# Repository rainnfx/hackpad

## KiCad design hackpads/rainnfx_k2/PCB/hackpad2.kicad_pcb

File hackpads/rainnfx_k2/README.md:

# rainnfx_k2

This is my second attempt at making a solid macropad, this time I'm going with a much more simple, yet effective approach.

## Features:
- EC11 Rotary encoder
- 6 Keys

## CAD Model:
Everything fits together using 4 M3 Bolts and heatset inserts.

It has 3 separate printed pieces. The base where the PCB will sit, the top cover, and a custom knob for the encoder.

[ img will go here ]

Made in Shapr3d.

## PCB
Here's my PCB! It was made in KiCad.

Schematic
[ img ]

PCB
[ img ]

## Firmware Overview
This hackpad uses [QMK](https://qmk.fm/) firmware for everything. 

- the rotary encoder changes volume. press to mute
- The 6 keys currently are sort of placeholders, since I have no clue what I'll assign them to yet (probably to open some apps or smth)!

## BOM:
Here should be everything you need to make this hackpad

- 6x Cherry MX Switches
- 6x DSA Keycaps
- 4x M3x5x4 Heatset inserts
- 4x M3x16mm SHCS Bolts
- 6x [MMSD4148T1G](https://www.digikey.ca/en/products/detail/onsemi/mmsd4148t1g/919705) Diodes.
- 1x [EC11E15204A3](https://www.digikey.ca/en/products/detail/alps-alpine/ec11e15204a3/21721644)
- 1x XIAO RP2040
- 1x Case (3 printed parts)

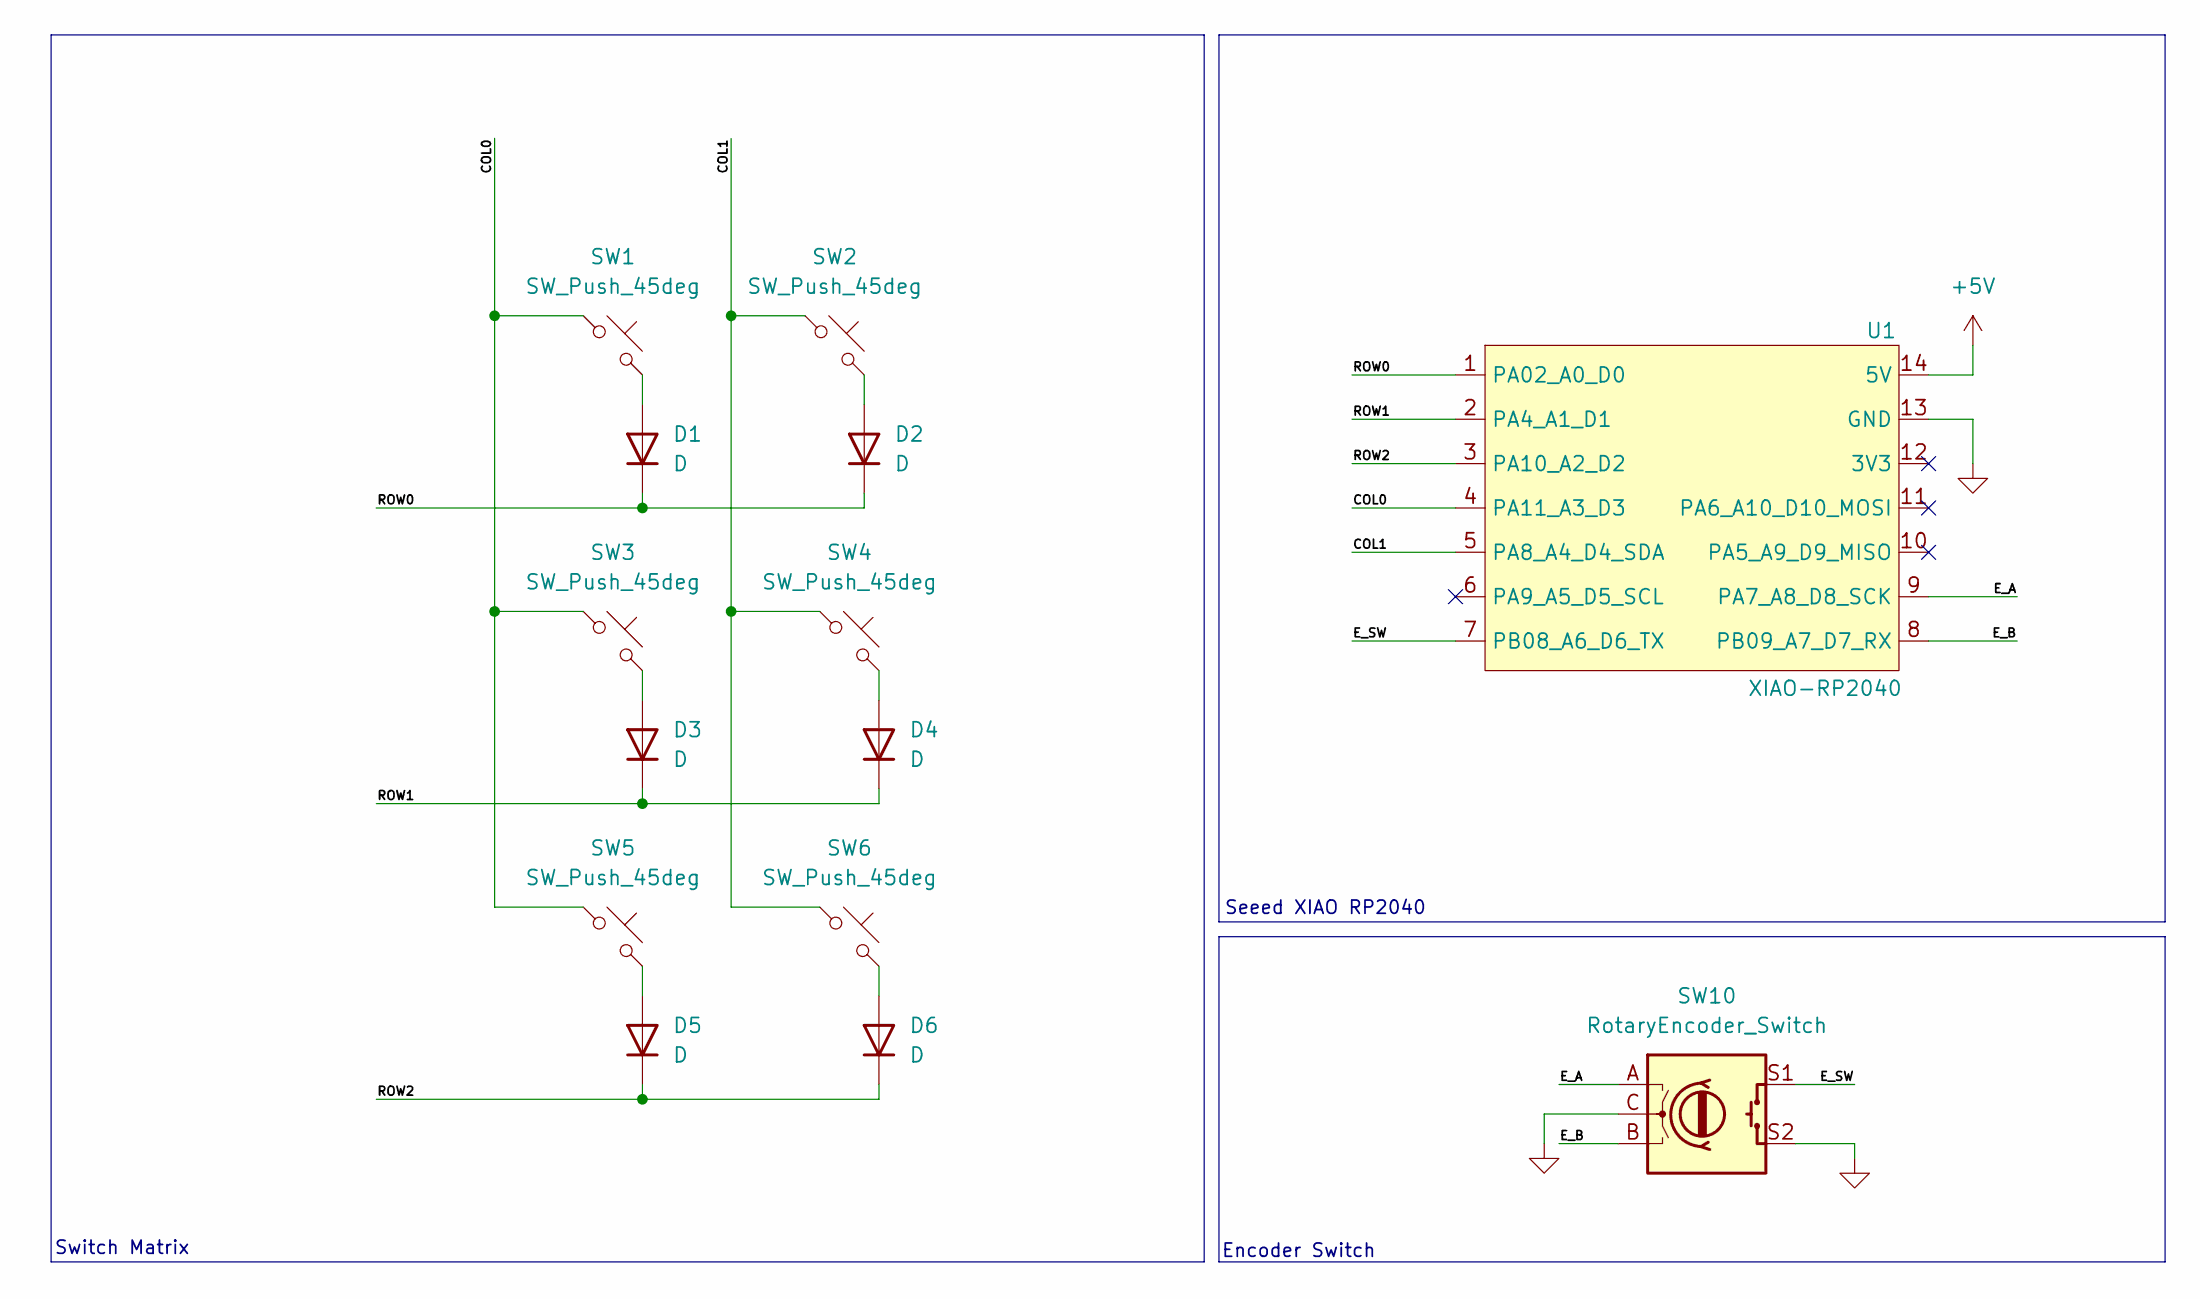
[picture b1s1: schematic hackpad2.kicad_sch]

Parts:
D1, D2, D3, D4, D5, D6: D; SOD3716X135N
SW1, SW2, SW3, SW4, SW5, SW6: SW_Push_45deg; SW_Cherry_MX_1.00u_PCB
SW10: RotaryEncoder_Switch; RotaryEncoder_Alps_EC11E-Switch_Vertical_H20mm
U1: XIAO-RP2040; MOUDLE14P-SMD-2.54-21X17.8MM

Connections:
+5V: U1.14 (5V)
/COL0: SW1.1, SW3.1, SW5.1, U1.4 (PA11_A3_D3)
/COL1: SW2.1, SW4.1, SW6.1, U1.5 (PA8_A4_D4_SDA)
/COL2: U1.6 (PA9_A5_D5_SCL)
/E_A: SW10.A, U1.9 (PA7_A8_D8_SCK)
/E_B: SW10.B, U1.8 (PB09_A7_D7_RX)
/E_SW: SW10.S1, U1.7 (PB08_A6_D6_TX)
/ROW0: D1.1 (K), D2.1 (K), U1.1 (PA02_A0_D0)
/ROW1: D3.1 (K), D4.1 (K), U1.2 (PA4_A1_D1)
/ROW2: D5.1 (K), D6.1 (K), U1.3 (PA10_A2_D2)
GND: SW10.C, SW10.S2, U1.13 (GND)
unnamed: D1.2 (A), SW1.2
unnamed: D2.2 (A), SW2.2
unnamed: D3.2 (A), SW3.2
unnamed: D4.2 (A), SW4.2
unnamed: D5.2 (A), SW5.2
unnamed: D6.2 (A), SW6.2

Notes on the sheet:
Seeed XIAO RP2040
Encoder Switch
Switch Matrix

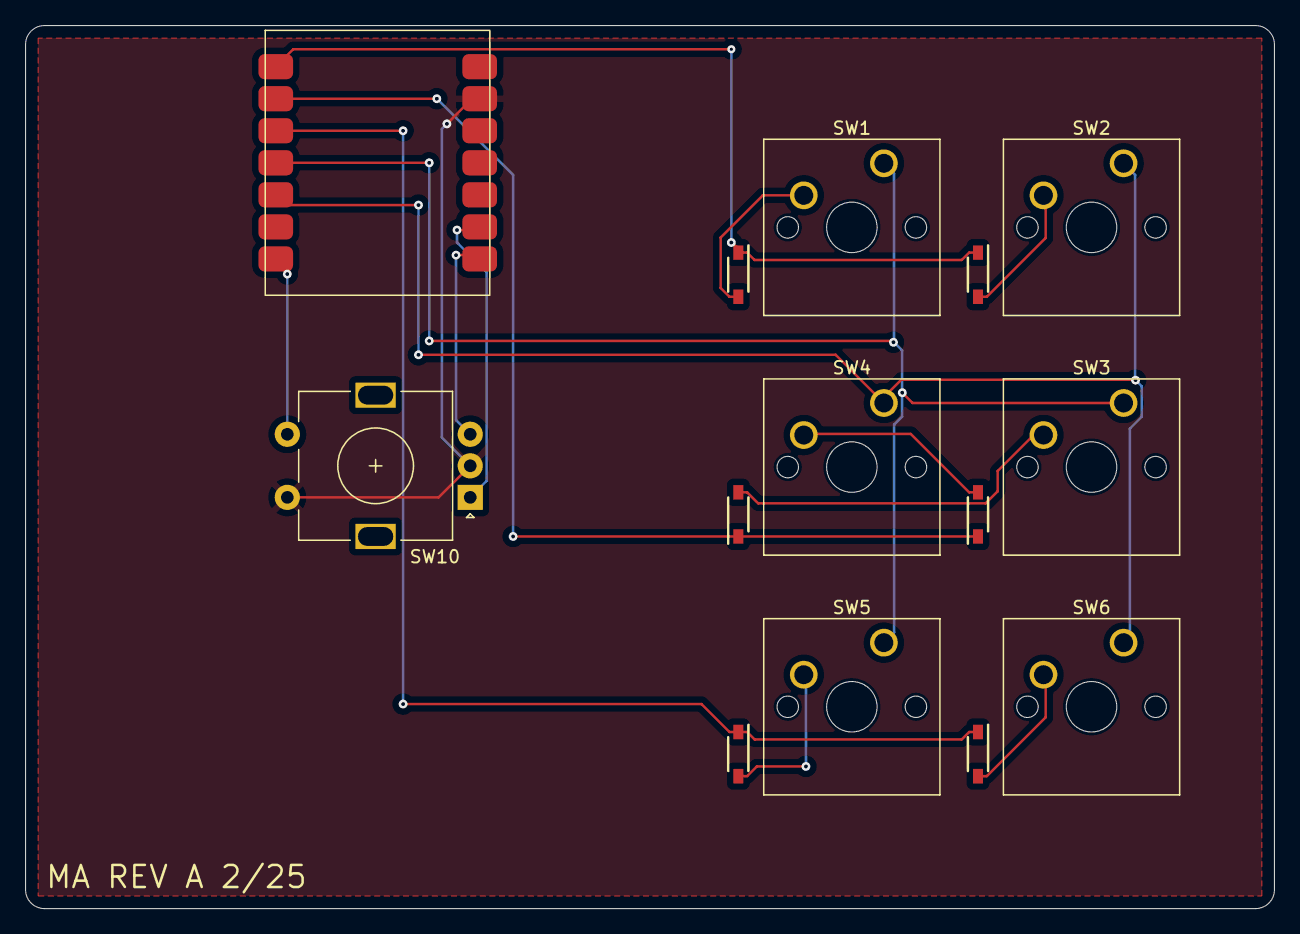
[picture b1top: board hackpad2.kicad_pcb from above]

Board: 2 copper layers, 99.0 x 70.0 mm, 14 parts (0 on the bottom side), 15 nets.

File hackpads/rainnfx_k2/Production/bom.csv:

Designator,Footprint,Quantity,Value,LCSC Part #
"D1, D2, D3, D4, D5, D6",SOD3716X135N,6,D,
"SW1, SW2, SW3, SW4, SW5, SW6",SW_Cherry_MX_1.00u_PCB,6,SW_Push_45deg,
SW10,RotaryEncoder_Alps_EC11E-Switch_Vertical_H20mm,1,RotaryEncoder_Switch,
U1,MOUDLE14P-SMD-2.54-21X17.8MM,1,XIAO-RP2040,
